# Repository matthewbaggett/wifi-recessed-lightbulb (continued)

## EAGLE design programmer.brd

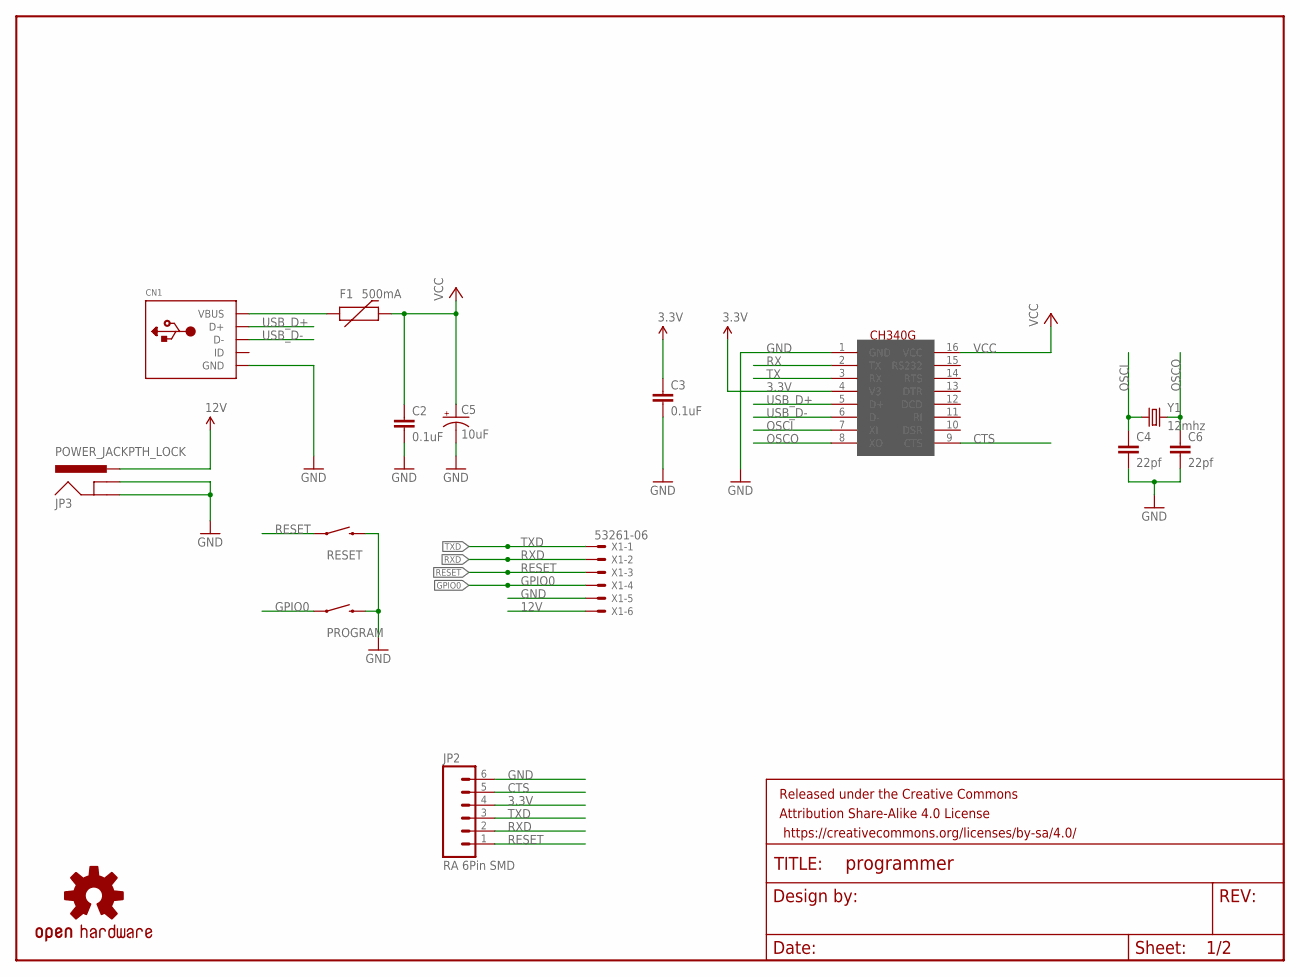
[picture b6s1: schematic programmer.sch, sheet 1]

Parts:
C2: 0.1uF; 1206
C3: 0.1uF; C1206K
C4, C6: 22pf; 1206
C5: 10uF; EIA3216
CN1: USBMINIB; USB-MINIB
F1: 500mA; PTC-1206
FRAME1: FRAME-LETTERNO_PACKAGE; DUMMY
JP2: RA 6Pin SMD; 1X06-SMD
JP3: POWER_JACKPTH_LOCK; POWER_JACK_PTH_LOCK
LOGO1: OSHW-LOGOS; OSHW-LOGO-S
PROGRAM: SWITCH-MOMENTARY-2PTH; TACTILE-PTH
RESET: SWITCH-MOMENTARY-2PTH; TACTILE-PTH
U$1: CH340G; SOIC16
X1: 53261-06
Y1: 12mhz; HC49UP

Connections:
3.3V: C3.1, JP2.4, U$1.4 (V3)
12V: JP3.PWR, X1.6
CTS: JP2.5, U$1.9 (CTS)
GND: C2.2, C3.2, C4.2, C5.C (-), C6.2, CN1.GND, JP2.6, JP3.GND, JP3.GNDBREAK, PROGRAM.3 (2), RESET.3 (2), U$1.1 (GND), X1.5
GPIO0: PROGRAM.1, X1.4
unnamed: CN1.VBUS, F1.1
OSCI: C4.1, U$1.7 (XI), Y1.1
OSCO: C6.1, U$1.8 (XO), Y1.2
RESET: JP2.1, RESET.1, X1.3
RX: U$1.2 (TX)
RXD: JP2.2, X1.2
TX: U$1.3 (RX)
TXD: JP2.3, X1.1
USB_D+: CN1.D+, U$1.5 (D+)
USB_D-: CN1.D-, U$1.6 (D-)
VCC: C2.1, C5.A (+), F1.2, U$1.16 (VCC)

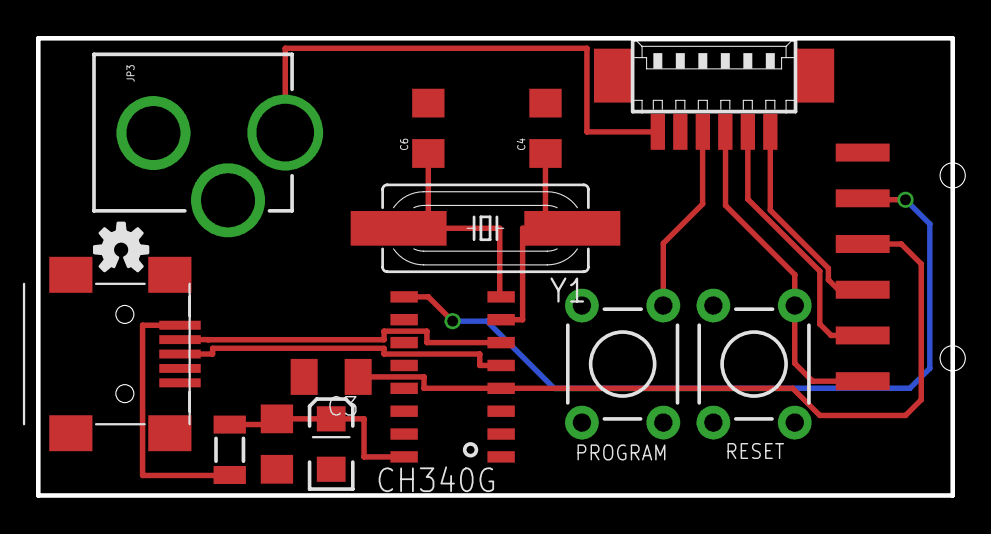
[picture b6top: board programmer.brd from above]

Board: 2 copper layers, 50.8 x 25.4 mm, 16 parts (0 on the bottom side), 14 nets.

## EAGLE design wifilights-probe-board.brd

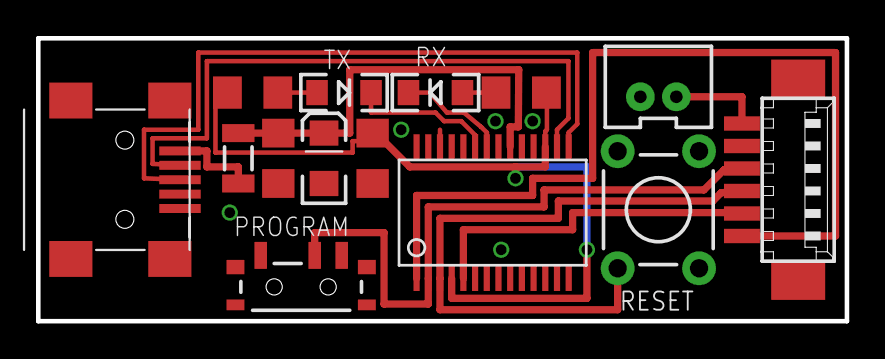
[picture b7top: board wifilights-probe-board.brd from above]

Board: 2 copper layers, 44.9 x 15.7 mm, 14 parts (0 on the bottom side), 15 nets.

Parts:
C1, C2: 0.1uF; 1206
C5: 10uF; EIA3216
CN1: USB-MINIB
F1: 500mA; PTC-1206
JP1: 12V DC; JST-2-PTH-VERT
PROGRAM: SWITCH-SPST-SMD-A
R1, R2: 330; 1206
RESET: SWITCH-MOMENTARY-2PTH; TACTILE-PTH
RX: GREEN; LED-1206
TX: RED; LED-1206
U1: FT232R; SSOP28DB
X1: 53261-06

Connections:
3.3V: C1.1, R1.2, R2.2, U1.4, U1.17
12V: JP1.2, X1.6
DTR: PROGRAM.2, U1.2, X1.4
GND: C1.2, C2.2, C5.C, CN1.GND, JP1.1, PROGRAM.3, RESET.3, U1.7, U1.18, U1.21, U1.25, U1.26, X1.5
unnamed: R1.1, TX.A
unnamed: R2.1, RX.A
unnamed: CN1.VBUS, F1.1
RTS: RESET.1, U1.3, X1.3
RXD: U1.5, X1.2
RXLED: RX.C, U1.22
TXD: U1.1, X1.1
TXLED: TX.C, U1.23
USB_D+: CN1.D+, U1.15
USB_D-: CN1.D-, U1.16
VCC: C2.1, C5.A, F1.2, U1.20

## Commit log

2015-07-26 Initial commit, DRC OK, lets see what oshpark make of it.
2015-07-26 Damnit, how was I supposed to power this thing?
2015-08-08 As ordered recently. Discovered that SOT-23's are puny and 4 Luxeon Rebels are overkill. And that Banggood has cheaper ESP8266 modules.
2015-08-08 Add a second ground plane on the top surface, pump it full of vias to help add thermal mass and heat spreading
2015-08-21 Adding pogopin contacts
2015-08-21 Add ground probe tag, drill locating hole in board.
2015-08-21 initial probe board
2015-08-21 add SCL & SDA pins pogopins for programming
2015-08-21 add TXD, RXD & GPIO0 pins pogopins for programming
2015-08-21 add GPIO2 pins pogopins for programming
2015-08-21 Probe board complete
2015-08-21 Adding shim to hold PCB in place ontop of probe board
2015-08-30 eagle.epf?
2015-08-30 adding resistor values and moved C4
2015-08-31 Swapped to using 12x Luxeon Rebels instead of the hard-to-solder consolidated package.
2015-08-31 Fix some DRC issues
2015-08-31 Shim made irrelevent
2015-08-31 Better probe board
2015-08-31 Removing labels of uselessness
2015-09-04 Rotate socket to allow it not to clip through one of the SOT-223 transitors
2015-10-05 Adding more signals to a better connector, moved THINKING LED to another GPIO due to conflict
2015-10-07 Added 3x4 pin headers. Added 2x i2c JST connectors.
2015-10-09 Mk6 complete & DRC'd
2015-10-09 Laughably out of date
2015-10-09 Renamed boards
2015-10-09 Made mofications to schematics for readability
2015-10-09 Adding png versions of files for github
2015-10-09 Remove eagle.epf
2015-10-10 Revision of programmer board to include a SMD 6 pin FTDI header.
2015-10-10 Set licence.
2015-11-20 Revised to use larger regulators, Revised to use 4 layers
2015-12-18 Updating, more lock files
2015-12-18 Mk8 gets its PCA9685 back, the older LED controller turned out to only have 2 channels of PWM available, which is insufficient. Respan this board with 3xRGB 5050's and 3xLuxeon rebels. reduced comple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
2015-12-18 Mk8 readme
2015-12-18 Add ICSP header. Resolves #5
2015-12-18 Changed to CH340G + Crystal instead of FT232RL Resolves #4. Using 12 Volt Barrel Jack Resolves #3. Moved to Omron 10xxx switches instead of slider, Resolves #1
2015-12-23 Move the power connector further away from the SOC
2016-04-17 A fresh start
2016-04-17 Revise all the things
2016-04-17 mk9 brah.
2016-07-16 Turn into a single board for devkit
2016-07-16 add label
2016-07-16 Initial firmware that scanned for a now defunct i2c device
2017-09-13 Put hole in middle of board (hurr durr donuts). Change to smaller mosfets. Add pulldown resistors.
2017-09-13 Reworking board to standardise on 1206 caps and resistors. Moving caps into the center where they'll clip through the hole in the top board. Move power connector to rear (duh). Remove i2c connectors.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
2017-09-14 Finalised board design
2017-10-01 mk10
